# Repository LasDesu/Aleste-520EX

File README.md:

# aleste520ex
Project to recreate home computer Aleste 520EX

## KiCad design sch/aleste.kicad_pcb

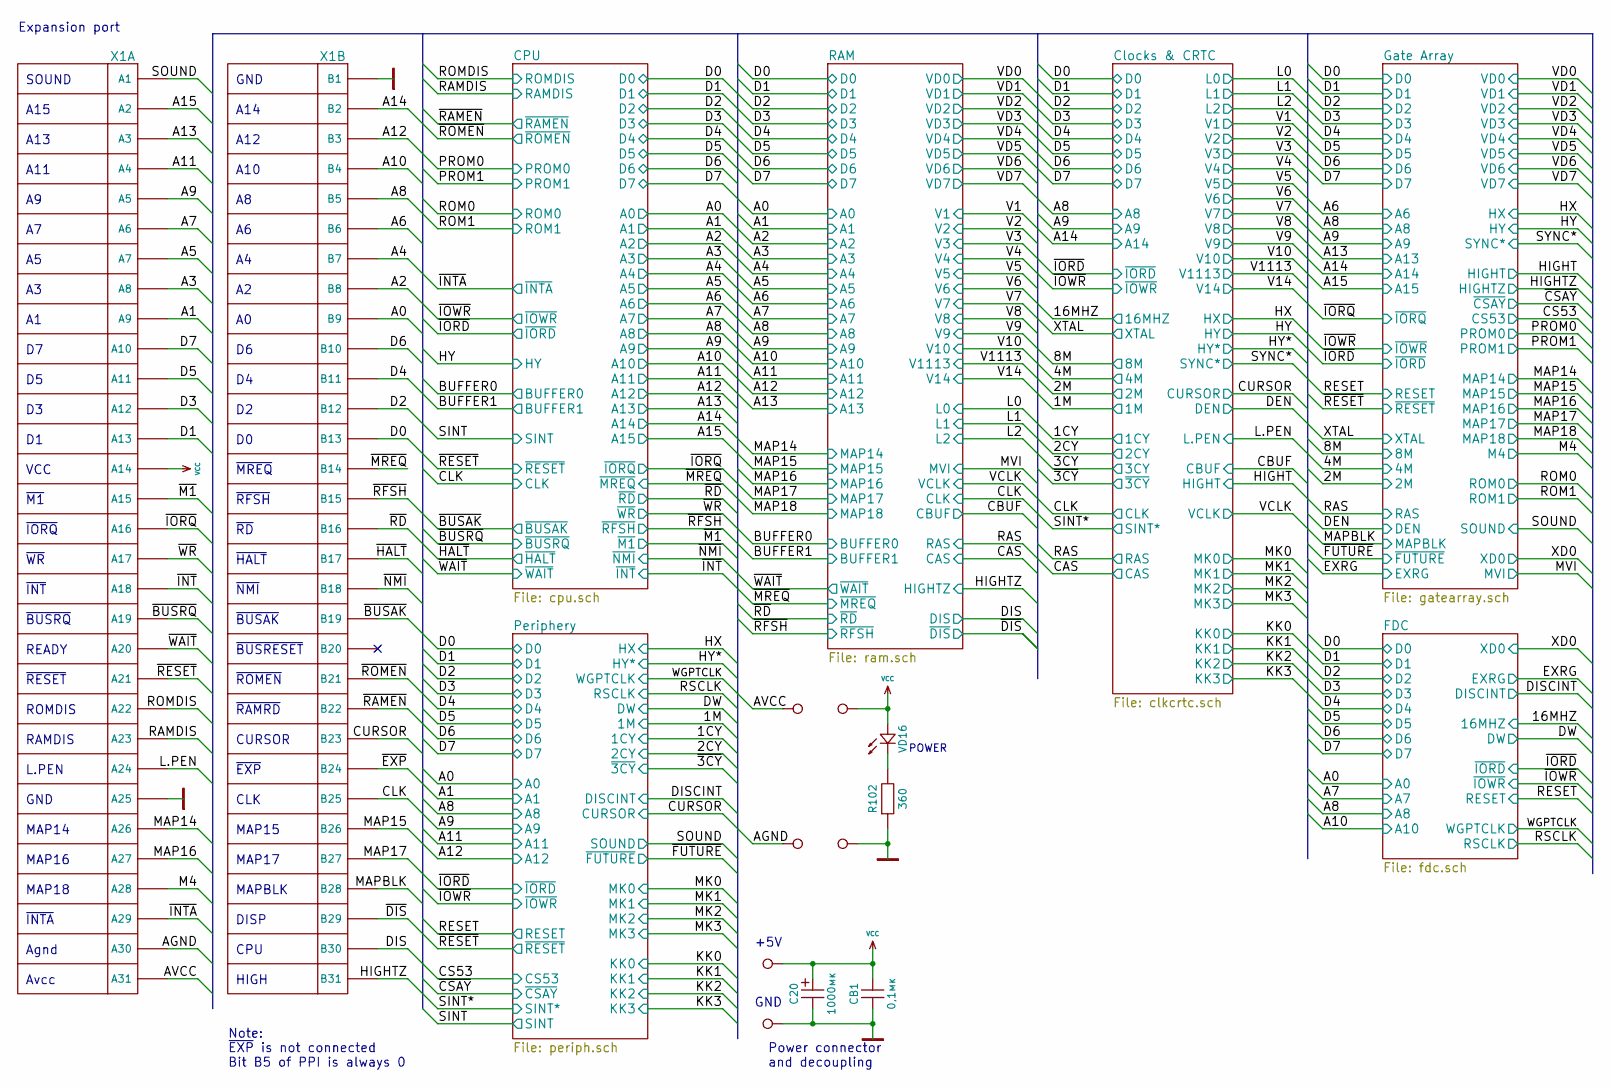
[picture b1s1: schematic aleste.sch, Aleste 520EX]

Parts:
C20: 1000мк; C_Radial_D10_L16_P5
CB1: 0,1мк; C_Disc_D7.5_P2.5
P1, P2, P3, P4, P5, P6: PIN
R102: 360; Resistor_Horizontal_RM7.5mm
VD16: LED_MY; Pin_Header_Straight_1x02
X1: SLOT-62; SLOT_62

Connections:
/A0: X1.B9; also elsewhere on the board
/A1: X1.A9; also elsewhere on the board
/A2: X1.B8; also elsewhere on the board
/A3: X1.A8; also elsewhere on the board
/A4: X1.B7; also elsewhere on the board
/A5: X1.A7; also elsewhere on the board
/A6: X1.B6; also elsewhere on the board
/A7: X1.A6; also elsewhere on the board
/A8: X1.B5; also elsewhere on the board
/A9: X1.A5; also elsewhere on the board
/A10: X1.B4; also elsewhere on the board
/A11: X1.A4; also elsewhere on the board
/A12: X1.B3; also elsewhere on the board
/A13: X1.A3; also elsewhere on the board
/A14: X1.B2; also elsewhere on the board
/A15: X1.A2; also elsewhere on the board
/AGND: P4.1, X1.A30
/AVCC: P3.1, X1.A31
/CLK: X1.B25; also elsewhere on the board
/CURSOR: X1.B23; also elsewhere on the board
/D0: X1.B13; also elsewhere on the board
/D1: X1.A13; also elsewhere on the board
/D2: X1.B12; also elsewhere on the board
/D3: X1.A12; also elsewhere on the board
/D4: X1.B11; also elsewhere on the board
/D5: X1.A11; also elsewhere on the board
/D6: X1.B10; also elsewhere on the board
/D7: X1.A10; also elsewhere on the board
/DIS: X1.B30; also elsewhere on the board
/HIGHTZ: X1.B31; also elsewhere on the board
/L.PEN: X1.A24; also elsewhere on the board
/M4: X1.A28; also elsewhere on the board
/MAP14: X1.A26; also elsewhere on the board
/MAP15: X1.B26; also elsewhere on the board
/MAP16: X1.A27; also elsewhere on the board
/MAP17: X1.B27; also elsewhere on the board
/MAPBLK: X1.B28; also elsewhere on the board
/RAMDIS: X1.A23; also elsewhere on the board
/ROMDIS: X1.A22; also elsewhere on the board
/SOUND: X1.A1; also elsewhere on the board
/~BUSAK: X1.B19; also elsewhere on the board
/~BUSRQ: X1.A19; also elsewhere on the board
/~DIS: X1.B29; also elsewhere on the board
/~EXP: X1.B24
/~HALT: X1.B17; also elsewhere on the board
/~INT: X1.A18; also elsewhere on the board
/~INTA: X1.A29; also elsewhere on the board
/~IORQ: X1.A16; also elsewhere on the board
/~M1: X1.A15; also elsewhere on the board
/~MREQ: X1.B14; also elsewhere on the board
/~NMI: X1.B18; also elsewhere on the board
/~RAMEN: X1.B22; also elsewhere on the board
/~RD: X1.B16; also elsewhere on the board
/~RESET: X1.A21; also elsewhere on the board
/~RFSH: X1.B15; also elsewhere on the board
/~ROMEN: X1.B21; also elsewhere on the board
/~WAIT: X1.A20; also elsewhere on the board
/~WR: X1.A17; also elsewhere on the board
GND: C20.2, CB1.1, P2.1, P6.1, R102.1, X1.A25, X1.B1; also elsewhere on the board
unnamed: R102.2, VD16.1
VCC: C20.1, CB1.2, P1.1, P5.1, VD16.2, X1.A14; also elsewhere on the board

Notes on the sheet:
POWER
Note: ~EXP~ is not connected Bit B5 of PPI is always 0
Expansion port
MAP18
DISP
CPU
HIGH
~RAMRD
~BUSRESET
Agnd
Avcc
READY
SOUND
GND
VCC
~INTA
MAPBLK
MAP17
MAP15
MAP16
MAP14
CLK
~EXP
L.PEN
CURSOR
RAMDIS
ROMDIS
~ROMEN
~RESET
~BUSAK
~BUSRQ
~NMI
~INT
~HALT
~WR
~RD
~IORQ
~RFSH
~M1
~MREQ

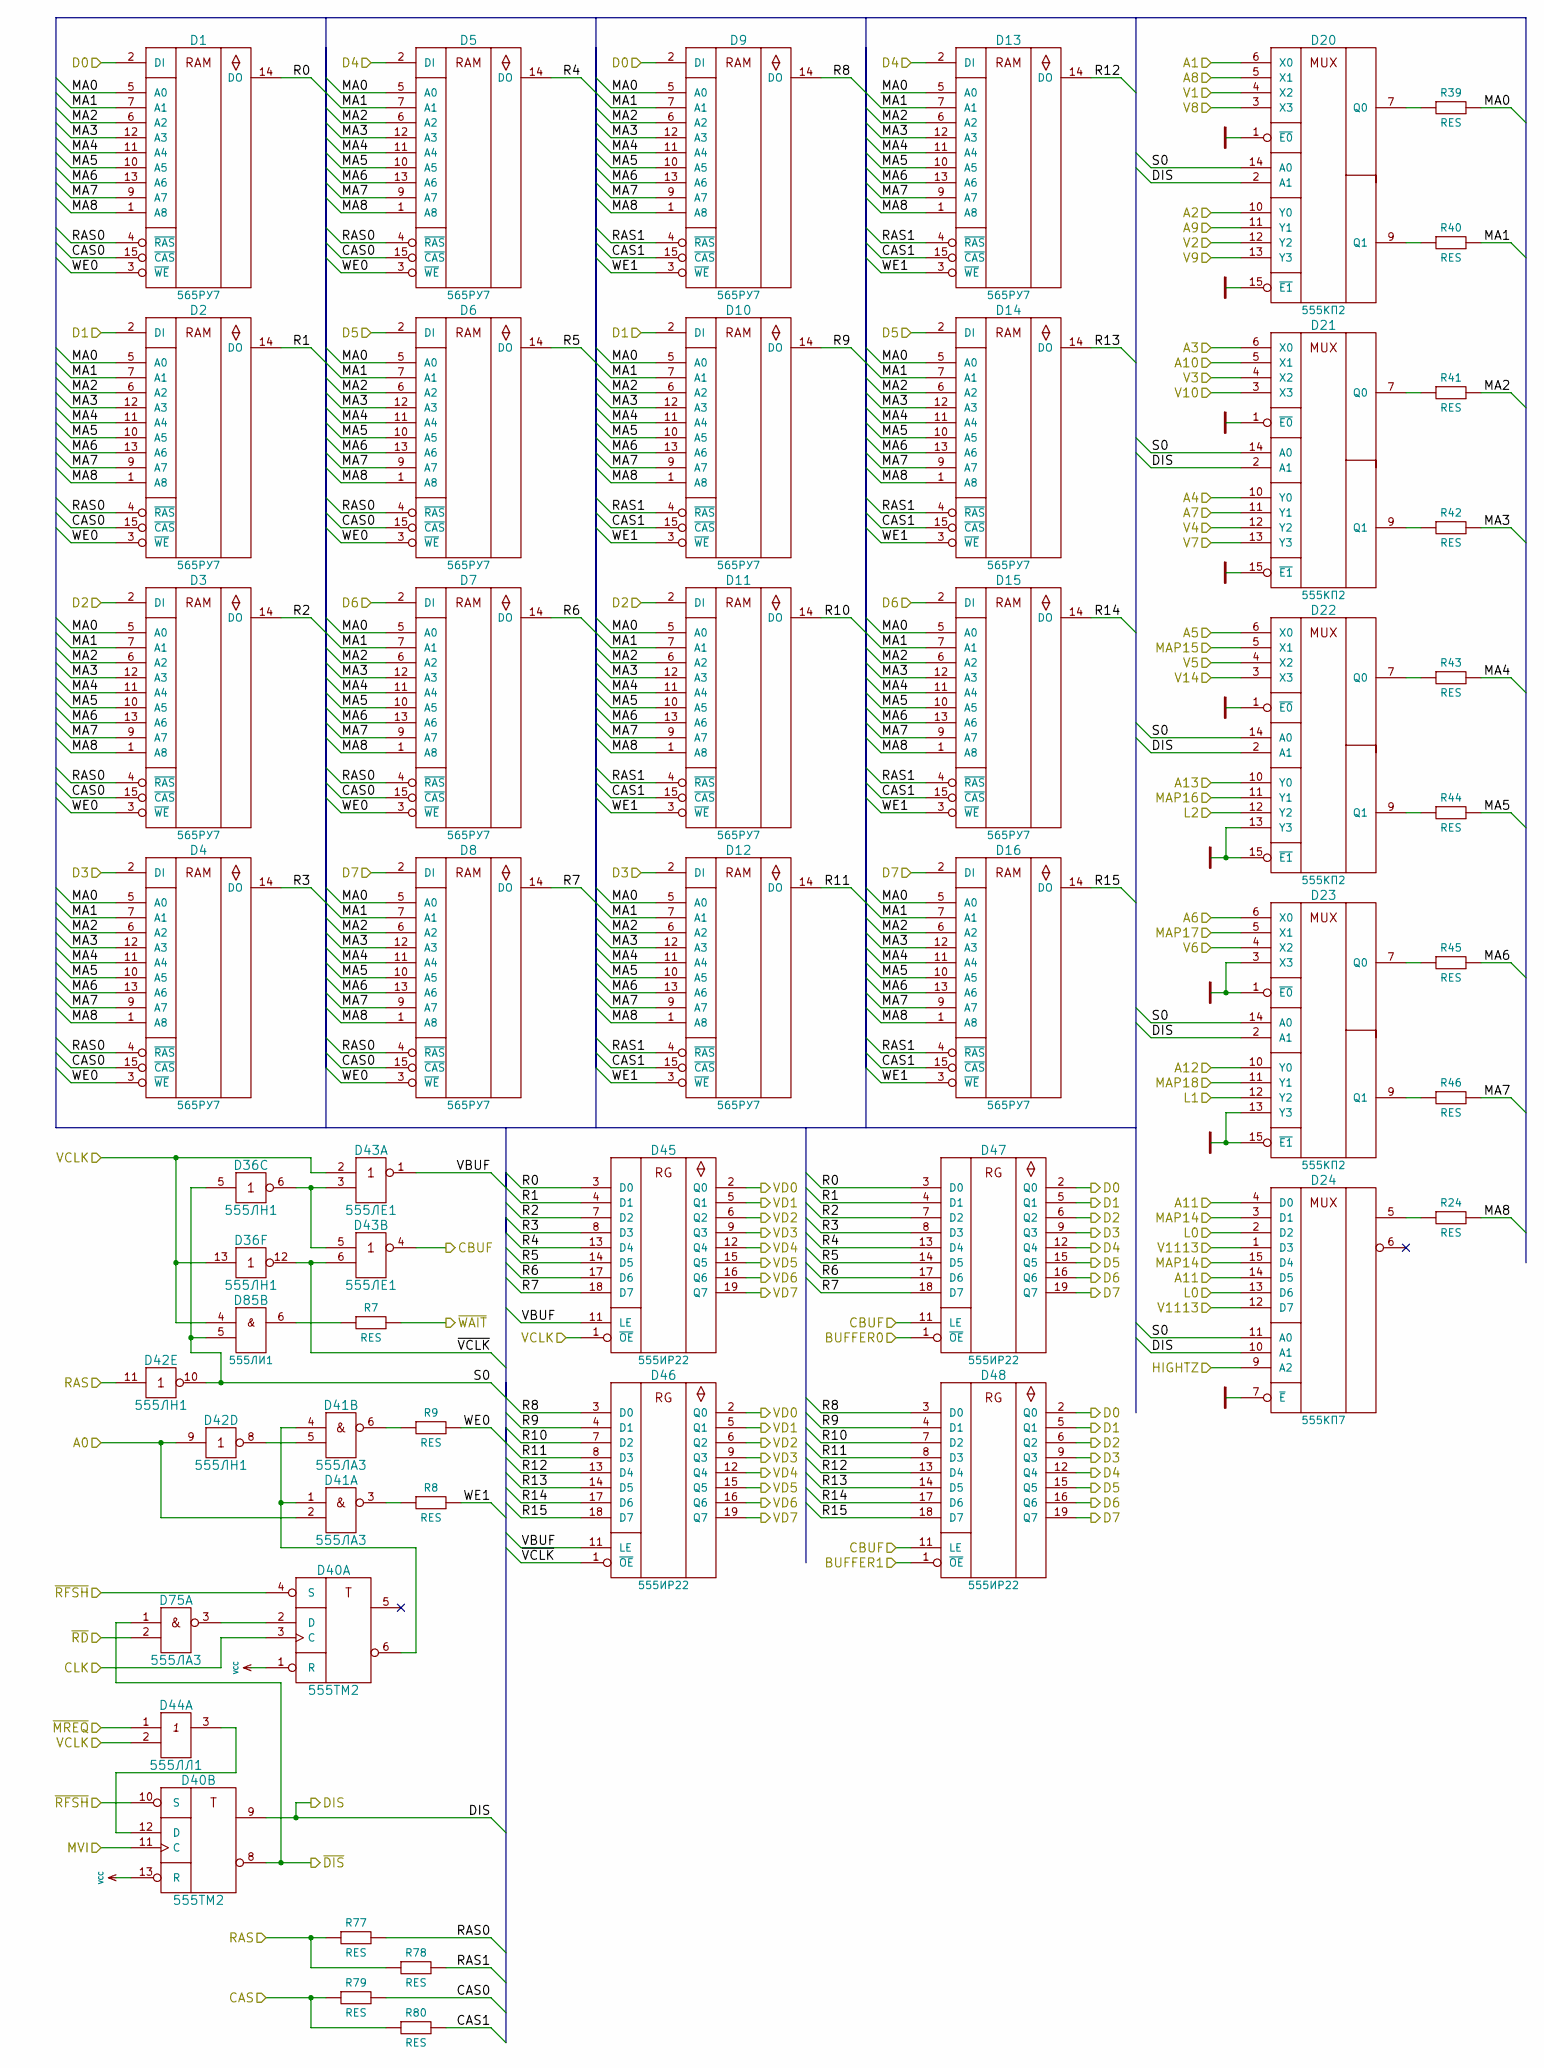
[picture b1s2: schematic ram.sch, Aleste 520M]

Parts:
D1, D2, D3, D4, D5, D6, D7, D8, D9, D10, D11, D12, D13, D14, D15, D16: 565РУ7; DIP-16
D20, D21, D22, D23: 555КП2; DIP-16
D24: 555КП7; DIP-16
D36, D42: 555ЛН1; DIP-14
D40: 555ТМ2; DIP-14
D41, D75: 555ЛА3; DIP-14
D43: 555ЛЕ1; DIP-14
D44: 555ЛЛ1; DIP-14
D45, D46, D47, D48: 555ИР22; DIP-20
D85: 555ЛИ1; DIP-14
R7, R8, R9, R24, R39, R40, R41, R42, R43, R44, R45, R46, R77, R78, R79, R80: RES; Resistor_Horizontal_RM7.5mm

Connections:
/A0: D41.2 (in2), D42.9 (in); also elsewhere on the board
/A1: D20.6 (X0); also elsewhere on the board
/A2: D20.10 (Y0); also elsewhere on the board
/A3: D21.6 (X0); also elsewhere on the board
/A4: D21.10 (Y0); also elsewhere on the board
/A5: D22.6 (X0); also elsewhere on the board
/A6: D23.6 (X0); also elsewhere on the board
/A7: D21.11 (Y1); also elsewhere on the board
/A8: D20.5 (X1); also elsewhere on the board
/A9: D20.11 (Y1); also elsewhere on the board
/A10: D21.5 (X1); also elsewhere on the board
/A11: D24.4 (D0), D24.14 (D5); also elsewhere on the board
/A12: D23.10 (Y0); also elsewhere on the board
/A13: D22.10 (Y0); also elsewhere on the board
/BUFFER0: D47.1 (~OE); also elsewhere on the board
/BUFFER1: D48.1 (~OE); also elsewhere on the board
/CAS: R79.1, R80.1; also elsewhere on the board
/CBUF: D43.4 (out), D47.11 (LE), D48.11 (LE); also elsewhere on the board
/CLK: D40.3 (C); also elsewhere on the board
/D0: D1.2 (DI), D9.2 (DI), D47.2 (Q0), D48.2 (Q0); also elsewhere on the board
/D1: D2.2 (DI), D10.2 (DI), D47.5 (Q1), D48.5 (Q1); also elsewhere on the board
/D2: D3.2 (DI), D11.2 (DI), D47.6 (Q2), D48.6 (Q2); also elsewhere on the board
/D3: D4.2 (DI), D12.2 (DI), D47.9 (Q3), D48.9 (Q3); also elsewhere on the board
/D4: D5.2 (DI), D13.2 (DI), D47.12 (Q4), D48.12 (Q4); also elsewhere on the board
/D5: D6.2 (DI), D14.2 (DI), D47.15 (Q5), D48.15 (Q5); also elsewhere on the board
/D6: D7.2 (DI), D15.2 (DI), D47.16 (Q6), D48.16 (Q6); also elsewhere on the board
/D7: D8.2 (DI), D16.2 (DI), D47.19 (Q7), D48.19 (Q7); also elsewhere on the board
/DIS: D20.2 (A1), D21.2 (A1), D22.2 (A1), D23.2 (A1), D24.10 (A1), D40.9; also elsewhere on the board
/HIGHTZ: D24.9 (A2); also elsewhere on the board
/L0: D24.2 (D2), D24.13 (D6); also elsewhere on the board
/L1: D23.12 (Y2); also elsewhere on the board
/L2: D22.12 (Y2); also elsewhere on the board
/MAP14: D24.3 (D1), D24.15 (D4); also elsewhere on the board
/MAP15: D22.5 (X1); also elsewhere on the board
/MAP16: D22.11 (Y1); also elsewhere on the board
/MAP17: D23.5 (X1); also elsewhere on the board
/MAP18: D23.11 (Y1); also elsewhere on the board
/MVI: D40.11 (C); also elsewhere on the board
/RAM/CAS0: D1.15 (~CAS), D2.15 (~CAS), D3.15 (~CAS), D4.15 (~CAS), D5.15 (~CAS), D6.15 (~CAS), D7.15 (~CAS), D8.15 (~CAS), R79.2
/RAM/CAS1: D9.15 (~CAS), D10.15 (~CAS), D11.15 (~CAS), D12.15 (~CAS), D13.15 (~CAS), D14.15 (~CAS), D15.15 (~CAS), D16.15 (~CAS), R80.2
/RAM/MA0: D1.5 (A0), D2.5 (A0), D3.5 (A0), D4.5 (A0), D5.5 (A0), D6.5 (A0), D7.5 (A0), D8.5 (A0), D9.5 (A0), D10.5 (A0), D11.5 (A0), D12.5 (A0), D13.5 (A0), D14.5 (A0), D15.5 (A0), D16.5 (A0), R39.2
/RAM/MA1: D1.7 (A1), D2.7 (A1), D3.7 (A1), D4.7 (A1), D5.7 (A1), D6.7 (A1), D7.7 (A1), D8.7 (A1), D9.7 (A1), D10.7 (A1), D11.7 (A1), D12.7 (A1), D13.7 (A1), D14.7 (A1), D15.7 (A1), D16.7 (A1), R40.2
/RAM/MA2: D1.6 (A2), D2.6 (A2), D3.6 (A2), D4.6 (A2), D5.6 (A2), D6.6 (A2), D7.6 (A2), D8.6 (A2), D9.6 (A2), D10.6 (A2), D11.6 (A2), D12.6 (A2), D13.6 (A2), D14.6 (A2), D15.6 (A2), D16.6 (A2), R41.2
/RAM/MA3: D1.12 (A3), D2.12 (A3), D3.12 (A3), D4.12 (A3), D5.12 (A3), D6.12 (A3), D7.12 (A3), D8.12 (A3), D9.12 (A3), D10.12 (A3), D11.12 (A3), D12.12 (A3), D13.12 (A3), D14.12 (A3), D15.12 (A3), D16.12 (A3), R42.2
/RAM/MA4: D1.11 (A4), D2.11 (A4), D3.11 (A4), D4.11 (A4), D5.11 (A4), D6.11 (A4), D7.11 (A4), D8.11 (A4), D9.11 (A4), D10.11 (A4), D11.11 (A4), D12.11 (A4), D13.11 (A4), D14.11 (A4), D15.11 (A4), D16.11 (A4), R43.2
/RAM/MA5: D1.10 (A5), D2.10 (A5), D3.10 (A5), D4.10 (A5), D5.10 (A5), D6.10 (A5), D7.10 (A5), D8.10 (A5), D9.10 (A5), D10.10 (A5), D11.10 (A5), D12.10 (A5), D13.10 (A5), D14.10 (A5), D15.10 (A5), D16.10 (A5), R44.2
/RAM/MA6: D1.13 (A6), D2.13 (A6), D3.13 (A6), D4.13 (A6), D5.13 (A6), D6.13 (A6), D7.13 (A6), D8.13 (A6), D9.13 (A6), D10.13 (A6), D11.13 (A6), D12.13 (A6), D13.13 (A6), D14.13 (A6), D15.13 (A6), D16.13 (A6), R45.2
/RAM/MA7: D1.9 (A7), D2.9 (A7), D3.9 (A7), D4.9 (A7), D5.9 (A7), D6.9 (A7), D7.9 (A7), D8.9 (A7), D9.9 (A7), D10.9 (A7), D11.9 (A7), D12.9 (A7), D13.9 (A7), D14.9 (A7), D15.9 (A7), D16.9 (A7), R46.2
/RAM/MA8: D1.1 (A8), D2.1 (A8), D3.1 (A8), D4.1 (A8), D5.1 (A8), D6.1 (A8), D7.1 (A8), D8.1 (A8), D9.1 (A8), D10.1 (A8), D11.1 (A8), D12.1 (A8), D13.1 (A8), D14.1 (A8), D15.1 (A8), D16.1 (A8), R24.2
/RAM/R0: D1.14 (DO), D45.3 (D0), D47.3 (D0)
/RAM/R1: D2.14 (DO), D45.4 (D1), D47.4 (D1)
/RAM/R2: D3.14 (DO), D45.7 (D2), D47.7 (D2)
/RAM/R3: D4.14 (DO), D45.8 (D3), D47.8 (D3)
/RAM/R4: D5.14 (DO), D45.13 (D4), D47.13 (D4)
/RAM/R5: D6.14 (DO), D45.14 (D5), D47.14 (D5)
/RAM/R6: D7.14 (DO), D45.17 (D6), D47.17 (D6)
/RAM/R7: D8.14 (DO), D45.18 (D7), D47.18 (D7)
/RAM/R8: D9.14 (DO), D46.3 (D0), D48.3 (D0)
/RAM/R9: D10.14 (DO), D46.4 (D1), D48.4 (D1)
/RAM/R10: D11.14 (DO), D46.7 (D2), D48.7 (D2)
/RAM/R11: D12.14 (DO), D46.8 (D3), D48.8 (D3)
/RAM/R12: D13.14 (DO), D46.13 (D4), D48.13 (D4)
/RAM/R13: D14.14 (DO), D46.14 (D5), D48.14 (D5)
/RAM/R14: D15.14 (DO), D46.17 (D6), D48.17 (D6)
/RAM/R15: D16.14 (DO), D46.18 (D7), D48.18 (D7)
/RAM/RAS0: D1.4 (~RAS), D2.4 (~RAS), D3.4 (~RAS), D4.4 (~RAS), D5.4 (~RAS), D6.4 (~RAS), D7.4 (~RAS), D8.4 (~RAS), R77.2
/RAM/RAS1: D9.4 (~RAS), D10.4 (~RAS), D11.4 (~RAS), D12.4 (~RAS), D13.4 (~RAS), D14.4 (~RAS), D15.4 (~RAS), D16.4 (~RAS), R78.2
/RAM/S0: D20.14 (A0), D21.14 (A0), D22.14 (A0), D23.14 (A0), D24.11 (A0), D36.5 (in), D42.10 (out), D85.5 (in2)
/RAM/VBUF: D43.1 (out), D45.11 (LE), D46.11 (LE)
/RAM/WE0: D1.3 (~WE), D2.3 (~WE), D3.3 (~WE), D4.3 (~WE), D5.3 (~WE), D6.3 (~WE), D7.3 (~WE), D8.3 (~WE), R9.2
/RAM/WE1: D9.3 (~WE), D10.3 (~WE), D11.3 (~WE), D12.3 (~WE), D13.3 (~WE), D14.3 (~WE), D15.3 (~WE), D16.3 (~WE), R8.2
/RAM/~VCLK: D36.12 (out), D43.6 (in2), D46.1 (~OE)
/RAS: D42.11 (in), R77.1, R78.1; also elsewhere on the board
/V1: D20.4 (X2); also elsewhere on the board
/V2: D20.12 (Y2); also elsewhere on the board
/V3: D21.4 (X2); also elsewhere on the board
/V4: D21.12 (Y2); also elsewhere on the board
/V5: D22.4 (X2); also elsewhere on the board
/V6: D23.4 (X2); also elsewhere on the board
/V7: D21.13 (Y3); also elsewhere on the board
/V8: D20.3 (X3); also elsewhere on the board
/V9: D20.13 (Y3); also elsewhere on the board
/V10: D21.3 (X3); also elsewhere on the board
/V14: D22.3 (X3); also elsewhere on the board
/V1113: D24.1 (D3), D24.12 (D7); also elsewhere on the board
/VCLK: D36.13 (in), D43.2 (in1), D44.2 (in2), D45.1 (~OE), D85.4 (in1); also elsewhere on the board
/VD0: D45.2 (Q0), D46.2 (Q0); also elsewhere on the board
/VD1: D45.5 (Q1), D46.5 (Q1); also elsewhere on the board
/VD2: D45.6 (Q2), D46.6 (Q2); also elsewhere on the board
/VD3: D45.9 (Q3), D46.9 (Q3); also elsewhere on the board
/VD4: D45.12 (Q4), D46.12 (Q4); also elsewhere on the board
/VD5: D45.15 (Q5), D46.15 (Q5); also elsewhere on the board
/VD6: D45.16 (Q6), D46.16 (Q6); also elsewhere on the board
/VD7: D45.19 (Q7), D46.19 (Q7); also elsewhere on the board
/~DIS: D40.8, D75.1 (in1); also elsewhere on the board
/~MREQ: D44.1 (in1); also elsewhere on the board
/~RD: D75.2 (in2); also elsewhere on the board
/~RFSH: D40.4 (S), D40.10 (S); also elsewhere on the board
/~WAIT: R7.2; also elsewhere on the board
GND: D1.16 (GND), D2.16 (GND), D3.16 (GND), D4.16 (GND), D5.16 (GND), D6.16 (GND), D7.16 (GND), D8.16 (GND), D9.16 (GND), D10.16 (GND), D11.16 (GND), D12.16 (GND), D13.16 (GND), D14.16 (GND), D15.16 (GND), D16.16 (GND), D20.1 (~E0), D20.8 (GND), D20.15 (~E1), D21.1 (~E0), D21.8 (GND), D21.15 (~E1), D22.1 (~E0), D22.8 (GND), D22.13 (Y3), D22.15 (~E1), D23.1 (~E0), D23.3 (X3), D23.8 (GND), D23.13 (Y3), D23.15 (~E1), D24.7 (~E), D24.8 (GND), D36.7 (GND), D40.7 (GND), D41.7 (GND), D42.7 (GND), D43.7 (GND), D44.7 (GND), D45.10 (GND), D46.10 (GND), D47.10 (GND), D48.10 (GND), D75.7 (GND), D85.7 (GND); also elsewhere on the board
unnamed: D20.7 (Q0), R39.1
unnamed: D20.9 (Q1), R40.1
unnamed: D21.7 (Q0), R41.1
unnamed: D21.9 (Q1), R42.1
unnamed: D22.7 (Q0), R43.1
unnamed: D22.9 (Q1), R44.1
unnamed: D23.7 (Q0), R45.1
unnamed: D23.9 (Q1), R46.1
unnamed: D24.5, R24.1
unnamed: D36.6 (out), D43.3 (in2), D43.5 (in1)
unnamed: D40.2 (D), D75.3 (out)
unnamed: D40.6, D41.1 (in1), D41.4 (in1)
unnamed: D40.12 (D), D44.3 (out)
unnamed: D41.3 (out), R8.1
unnamed: D41.5 (in2), D42.8 (out)
unnamed: D41.6 (out), R9.1
unnamed: D85.6 (out), R7.1
VCC: D1.8 (VCC), D2.8 (VCC), D3.8 (VCC), D4.8 (VCC), D5.8 (VCC), D6.8 (VCC), D7.8 (VCC), D8.8 (VCC), D9.8 (VCC), D10.8 (VCC), D11.8 (VCC), D12.8 (VCC), D13.8 (VCC), D14.8 (VCC), D15.8 (VCC), D16.8 (VCC), D20.16 (VCC), D21.16 (VCC), D22.16 (VCC), D23.16 (VCC), D24.16 (VCC), D36.14 (VCC), D40.1 (R), D40.13 (R), D40.14 (VCC), D41.14 (VCC), D42.14 (VCC), D43.14 (VCC), D44.14 (VCC), D45.20 (VCC), D46.20 (VCC), D47.20 (VCC), D48.20 (VCC), D75.14 (VCC), D85.14 (VCC); also elsewhere on the board

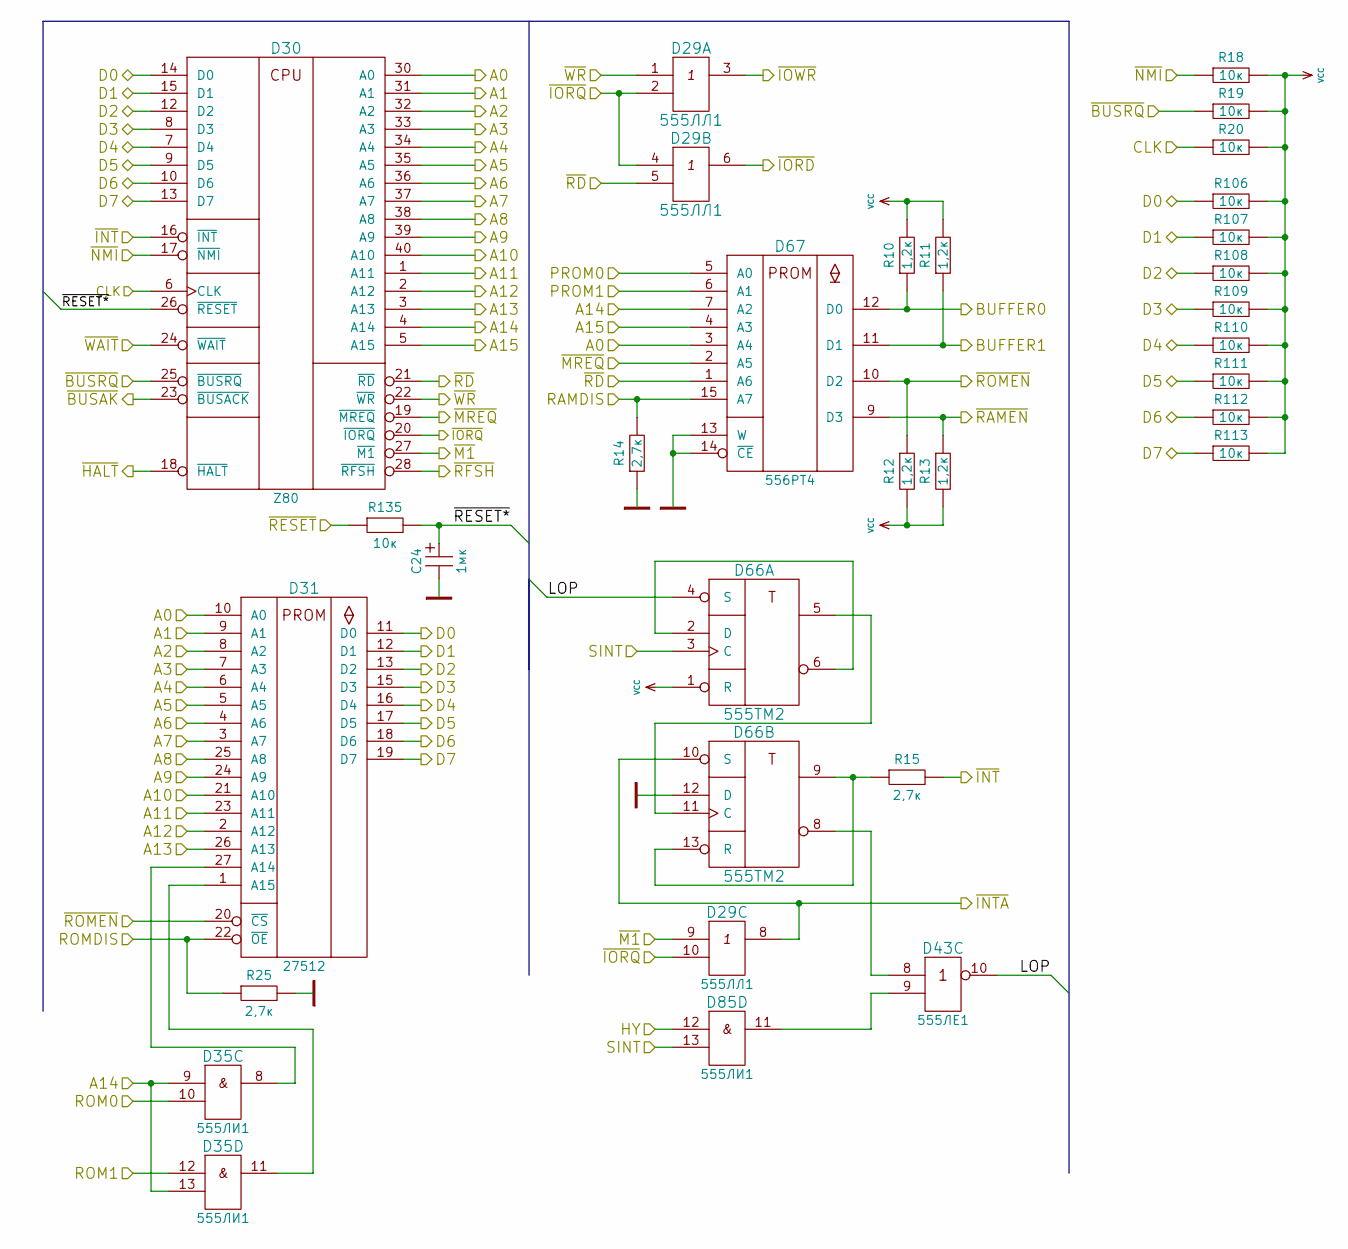
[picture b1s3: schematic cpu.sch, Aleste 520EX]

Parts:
C24: 1мк; C_Radial_D5_L6_P2.5
D29: 555ЛЛ1; DIP-14
D30: Z80; DIP-40
D31: 27512; DIP-28
D35, D85: 555ЛИ1; DIP-14
D43: 555ЛЕ1; DIP-14
D66: 555ТМ2; DIP-14
D67: 556РТ4; DIP-16
R10, R11, R12, R13: 1,2к; Resistor_Vertical_RM2.5mm
R14, R15, R25: 2,7к; Resistor_Horizontal_RM7.5mm
R18, R19, R20, R106, R107, R108, R109, R110, R111, R112, R113: 10к; Resistor_Vertical_RM2.5mm
R135: 10к; Resistor_Horizontal_RM7.5mm

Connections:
/A0: D30.30 (A0), D31.10 (A0), D67.3 (A4); also elsewhere on the board
/A1: D30.31 (A1), D31.9 (A1); also elsewhere on the board
/A2: D30.32 (A2), D31.8 (A2); also elsewhere on the board
/A3: D30.33 (A3), D31.7 (A3); also elsewhere on the board
/A4: D30.34 (A4), D31.6 (A4); also elsewhere on the board
/A5: D30.35 (A5), D31.5 (A5); also elsewhere on the board
/A6: D30.36 (A6), D31.4 (A6); also elsewhere on the board
/A7: D30.37 (A7), D31.3 (A7); also elsewhere on the board
/A8: D30.38 (A8), D31.25 (A8); also elsewhere on the board
/A9: D30.39 (A9), D31.24 (A9); also elsewhere on the board
/A10: D30.40 (A10), D31.21 (A10); also elsewhere on the board
/A11: D30.1 (A11), D31.23 (A11); also elsewhere on the board
/A12: D30.2 (A12), D31.2 (A12); also elsewhere on the board
/A13: D30.3 (A13), D31.26 (A13); also elsewhere on the board
/A14: D30.4 (A14), D35.9 (in1), D35.13 (in2), D67.7 (A2); also elsewhere on the board
/A15: D30.5 (A15), D67.4 (A3); also elsewhere on the board
/BUFFER0: D67.12 (D0), R10.1; also elsewhere on the board
/BUFFER1: D67.11 (D1), R11.1; also elsewhere on the board
/CLK: D30.6 (CLK), R20.1; also elsewhere on the board
/CPU/LOP: D43.10 (out), D66.4 (S)
/CPU/~RESET*: C24.1, D30.26 (~RESET), R135.2
/D0: D30.14 (D0), D31.11 (D0), R106.1; also elsewhere on the board
/D1: D30.15 (D1), D31.12 (D1), R107.1; also elsewhere on the board
/D2: D30.12 (D2), D31.13 (D2), R108.1; also elsewhere on the board
/D3: D30.8 (D3), D31.15 (D3), R109.1; also elsewhere on the board
/D4: D30.7 (D4), D31.16 (D4), R110.1; also elsewhere on the board
/D5: D30.9 (D5), D31.17 (D5), R111.1; also elsewhere on the board
/D6: D30.10 (D6), D31.18 (D6), R112.1; also elsewhere on the board
/D7: D30.13 (D7), D31.19 (D7), R113.1; also elsewhere on the board
/HY: D85.12 (in1); also elsewhere on the board
/PROM0: D67.5 (A0); also elsewhere on the board
/PROM1: D67.6 (A1); also elsewhere on the board
/RAMDIS: D67.15 (A7), R14.2; also elsewhere on the board
/ROM0: D35.10 (in2); also elsewhere on the board
/ROM1: D35.12 (in1); also elsewhere on the board
/ROMDIS: D31.22 (~OE), R25.1; also elsewhere on the board
/SINT: D66.3 (C), D85.13 (in2); also elsewhere on the board
/~BUSAK: D30.23 (~BUSACK); also elsewhere on the board
/~BUSRQ: D30.25 (~BUSRQ), R19.1; also elsewhere on the board
/~HALT: D30.18 (~HALT); also elsewhere on the board
/~INT: D30.16 (~INT), R15.2; also elsewhere on the board
/~INTA: D29.8 (out), D66.10 (S); also elsewhere on the board
/~IORD: D29.6 (out); also elsewhere on the board
/~IORQ: D29.2 (in2), D29.4 (in1), D29.10 (in2), D30.20 (~IORQ); also elsewhere on the board
/~IOWR: D29.3 (out); also elsewhere on the board
/~M1: D29.9 (in1), D30.27 (~M1); also elsewhere on the board
/~MREQ: D30.19 (~MREQ), D67.2 (A5); also elsewhere on the board
/~NMI: D30.17 (~NMI), R18.1; also elsewhere on the board
/~RAMEN: D67.9 (D3), R13.1; also elsewhere on the board
/~RD: D29.5 (in2), D30.21 (~RD), D67.1 (A6); also elsewhere on the board
/~RESET: R135.1; also elsewhere on the board
/~RFSH: D30.28 (~RFSH); also elsewhere on the board
/~ROMEN: D31.20 (~CS), D67.10 (D2), R12.1; also elsewhere on the board
/~WAIT: D30.24 (~WAIT); also elsewhere on the board
/~WR: D29.1 (in1), D30.22 (~WR); also elsewhere on the board
GND: C24.2, D29.7 (GND), D30.29 (GND), D31.14 (GND), D35.7 (GND), D43.7 (GND), D66.7 (GND), D66.12 (D), D67.8 (GND), D67.13 (W), D67.14 (~CE), D85.7 (GND), R14.1, R25.2; also elsewhere on the board
unnamed: D31.1 (A15), D35.11 (out)
unnamed: D31.27 (A14), D35.8 (out)
unnamed: D43.8 (in1), D66.8
unnamed: D43.9 (in2), D85.11 (out)
unnamed: D66.2 (D), D66.6
unnamed: D66.5, D66.11 (C)
unnamed: D66.9, D66.13 (R), R15.1
VCC: D29.14 (VCC), D30.11 (VCC), D31.28 (VCC), D35.14 (VCC), D43.14 (VCC), D66.1 (R), D66.14 (VCC), D67.16 (VCC), D85.14 (VCC), R10.2, R11.2, R12.2, R13.2, R18.2, R19.2, R20.2, R106.2, R107.2, R108.2, R109.2, R110.2, R111.2, R112.2, R113.2; also elsewhere on the board
